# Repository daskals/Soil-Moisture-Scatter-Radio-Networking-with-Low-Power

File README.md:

# Soil-Moisture-Scatter-Radio-Networking-with-Low-Power
Hardware and Software files of  IEEE publication: Soil Moisture Scatter Radio Networking with Low Power

In this repo, a low-cost (6 Euro per sensor), low-power (in the order of 200 µW per sensor), with high communication range (in the order of 250 meter), scatter radio sensor network is presented, for soil moisture monitoring at multiple locations. The proposed network utilizes analog frequency modulation (FM) in a bistatic network
architecture (i.e., the emitter and reader are not co-located), while
the sensors operate simultaneously, using frequency division
multiple access (FDMA). In contrast to prior art, this work
utilizes an ultra-low cost software-defined radio reader, offers
custom microstrip capacitive sensing with simple calibration, as
well as modulation pulses for each scatter radio sensor with
50% duty cycle; the latter is necessary for scalable network
designs. Overall root mean squared error (RMSE) below 1% is observed, even for ranges of 250 m. This is another small (but concrete) step for the adoption of scatter radio technology as a
key enabling technology for scalable, large-scale, low-power and cost environmental sensor networking.
---

IEEE Xplore: https://ieeexplore.ieee.org/document/7490345/ \
Local: http://www.daskalakispiros.com/files/daskalakis_mtt_2015.pdf

---
**Questions/issues**
Inquiries regarding the scripts provided are cordially welcome.

---
**Citing**

If you use our algorithm, please cite [[1]](https://ieeexplore.ieee.org/document/7490345/).

```bibtex
@article{daskalakis2016soil,
  title={Soil moisture scatter radio networking with low power},
  author={Daskalakis, Spyridon-Nektarios and Assimonis, Stylianos D and Kampianakis, Eleftherios and Bletsas, Aggelos},
  journal={IEEE Transactions on Microwave Theory and Techniques},
  volume={64},
  number={7},
  pages={2338--2346},
  year={2016},
  publisher={IEEE}
}
 
```

[[1]](https://ieeexplore.ieee.org/document/7490345/) S. N. Daskalakis, S.D. Assimonis, E. Kampianakis and A. Bletsas, Soil Moisture Scatter Radio Networking with Low Power, IEEE Transactions on Microwave Theory and Techniques (TMTT), Special Issue on RFID Sensing & Imaging, Vol. 64, No. 7, pp. 2338-2346, July 2016.

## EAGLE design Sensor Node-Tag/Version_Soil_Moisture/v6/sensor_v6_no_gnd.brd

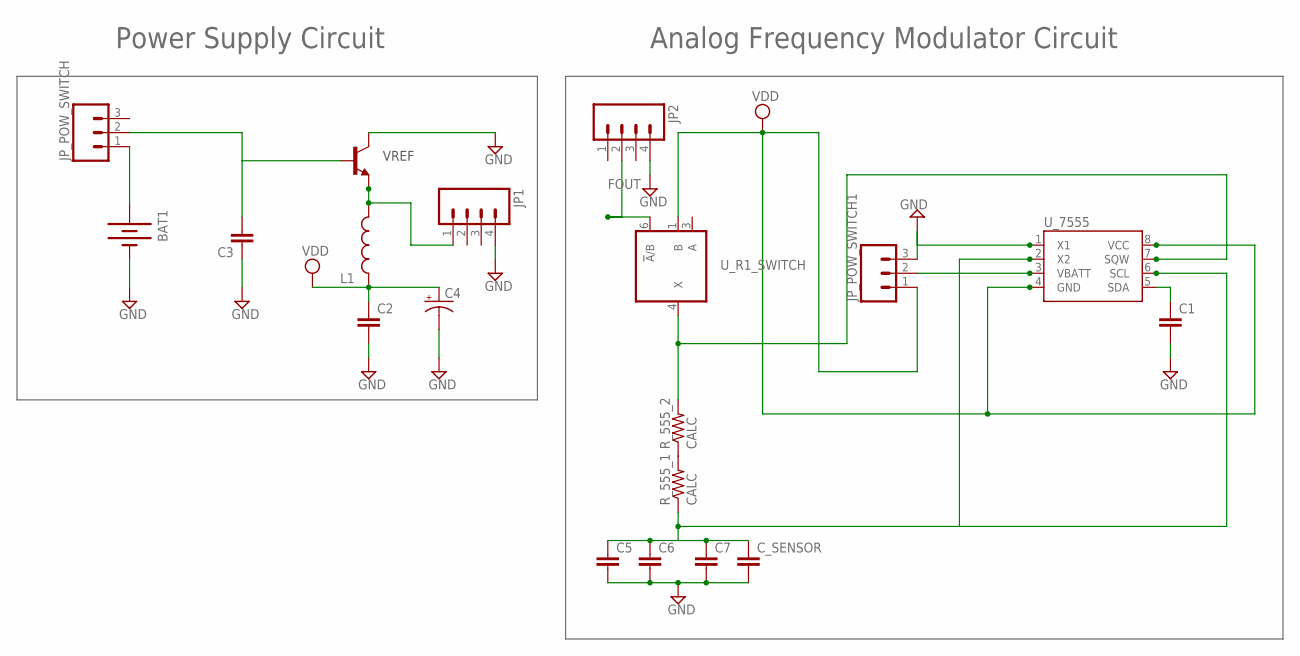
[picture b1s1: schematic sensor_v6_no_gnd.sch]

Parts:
BAT1: BATTERY20PTH_LAB; BATTCOM_20MM_PTH
C1, C2, C3: CAP0603-CAP; 0603-CAP
C4: CAP_POL1206; EIA3216
C5, C6, C7: CAP0805; 0805
C_SENSOR: CAP0805; 0805
JP1, JP2: M04LOCK; 1X04_LOCK
JP_POW_SWITCH, JP_POW_SWITCH1: M03LOCK; 1X03_LOCK
L1: INDUCTOR0603; 0603
R_555_1, R_555_2: CALC; 0805
U_7555: DS1307SO8; SO08
U_R1_SWITCH: 741G3157DCKR; DCK_R-PDSO-G6
U_VREF: TRANSISTOR_NPNSOT23-3; SOT23-3

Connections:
FOUT: JP2.2, JP_POW_SWITCH1.2, U_7555.3 (VBATT), U_R1_SWITCH.6 (!A!/B)
GND: BAT1.2 (-), C1.2, C2.2, C3.1, C4.C (-), C5.2, C6.2, C7.2, C_SENSOR.2, JP1.4, JP2.4, JP_POW_SWITCH1.3, U_7555.1 (X1), U_R1_SWITCH.2 (GND), U_VREF.3 (C)
unnamed: BAT1.1 (+), JP_POW_SWITCH.1
unnamed: R_555_1.2, R_555_2.1
P2: C5.1, C6.1, C7.1, C_SENSOR.1, R_555_1.1, U_7555.2 (X2), U_7555.6 (SCL)
P5: C1.1, U_7555.5 (SDA)
P7: R_555_2.2, U_7555.7 (SQW), U_R1_SWITCH.4 (X)
VCC: U_R1_SWITCH.5 (VCC)
VDD: C2.1, C4.A (+), JP_POW_SWITCH1.1, L1.1, U_7555.4 (GND), U_7555.8 (VCC), U_R1_SWITCH.1 (B)
VREFIN: C3.2, JP_POW_SWITCH.2, U_VREF.1 (B)
VREFOUT: JP1.1, L1.2, U_VREF.2 (E)

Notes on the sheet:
Power Supply Circuit
Analog Frequency Modulator Circuit
VREF

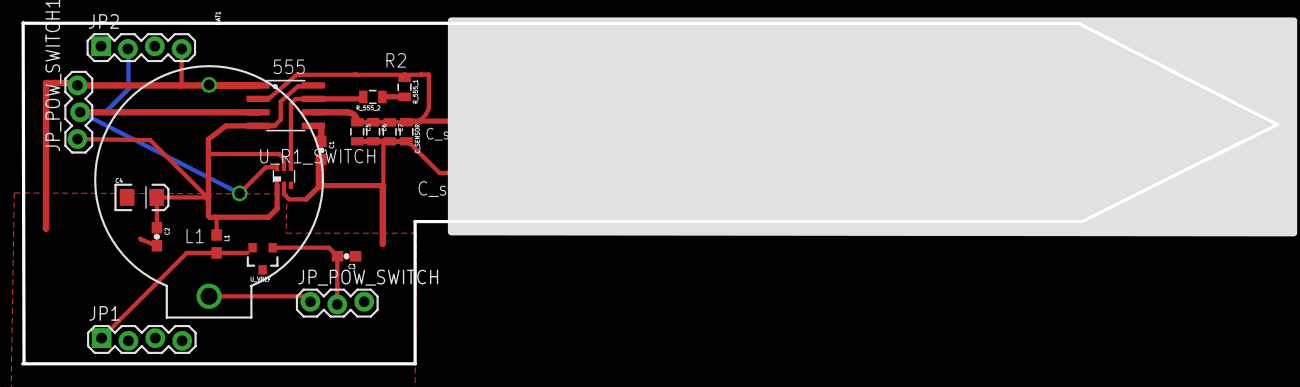
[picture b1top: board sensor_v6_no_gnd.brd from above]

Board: 2 copper layers, 118.6 x 32.2 mm, 19 parts (0 on the bottom side), 10 nets.

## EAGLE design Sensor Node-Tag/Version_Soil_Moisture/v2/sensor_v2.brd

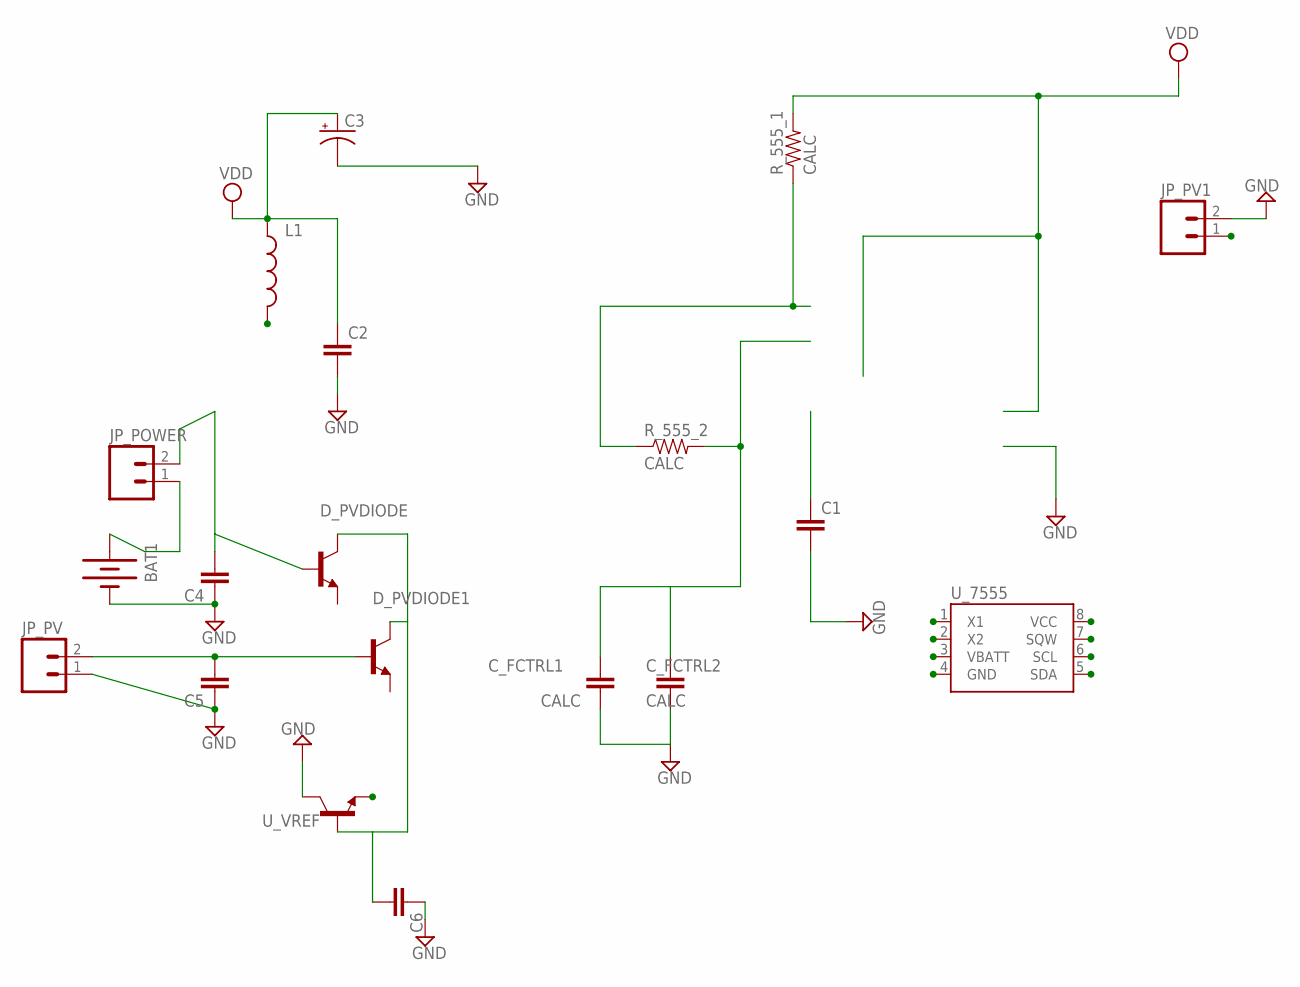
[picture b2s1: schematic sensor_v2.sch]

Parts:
BAT1: BATTERY20PTH_LAB; BATTCOM_20MM_PTH
C1, C2, C4, C5, C6: CAP0603-CAP; 0603-CAP
C3: CAP_POL1206; EIA3216
C_FCTRL1, C_FCTRL2: CALC; 0603-CAP
D_PVDIODE, D_PVDIODE1: TRANSISTOR_NPNSOT23-3; SOT23-3
JP_POWER: M02LOCK; 1X02_LOCK
JP_PV, JP_PV1: M02LOCK; 1X02_LOCK
L1: INDUCTOR0603; 0603
R_555_1: CALC; 0805
R_555_2: CALC; 0603-RES
U_7555: DS1307SO8; SO08
U_VREF: TRANSISTOR_NPNSOT23-3; SOT23-3

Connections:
FOUT: JP_PV1.1, U_7555.3 (VBATT)
GND: BAT1.2 (-), C1.2, C2.2, C3.C (-), C4.1, C5.1, C6.1, C_FCTRL1.2, C_FCTRL2.2, JP_PV.1, JP_PV1.2, U_7555.1 (X1), U_VREF.3 (C)
unnamed: C5.2, D_PVDIODE1.1 (B), JP_PV.2
unnamed: BAT1.1 (+), JP_POWER.1
unnamed: C4.2, D_PVDIODE.1 (B), JP_POWER.2
P2: C_FCTRL1.1, C_FCTRL2.1, R_555_2.2, U_7555.2 (X2), U_7555.6 (SCL)
P5: C1.1, U_7555.5 (SDA)
P7: R_555_1.1, R_555_2.1, U_7555.7 (SQW)
VDD: C2.1, C3.A (+), L1.1, R_555_1.2, U_7555.4 (GND), U_7555.8 (VCC)
VREFIN: C6.2, D_PVDIODE.3 (C), D_PVDIODE1.3 (C), U_VREF.1 (B)
VREFOUT: L1.2, U_VREF.2 (E)

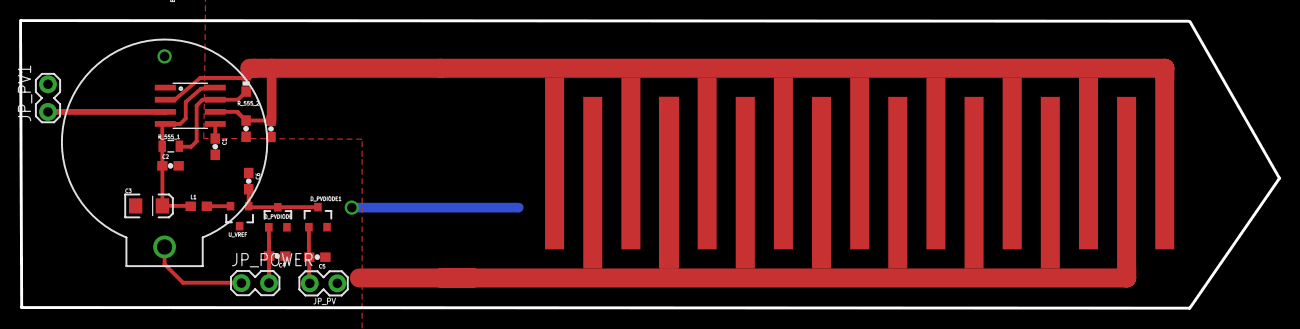
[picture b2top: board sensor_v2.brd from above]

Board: 2 copper layers, 132.1 x 30.2 mm, 19 parts (0 on the bottom side), 11 nets.

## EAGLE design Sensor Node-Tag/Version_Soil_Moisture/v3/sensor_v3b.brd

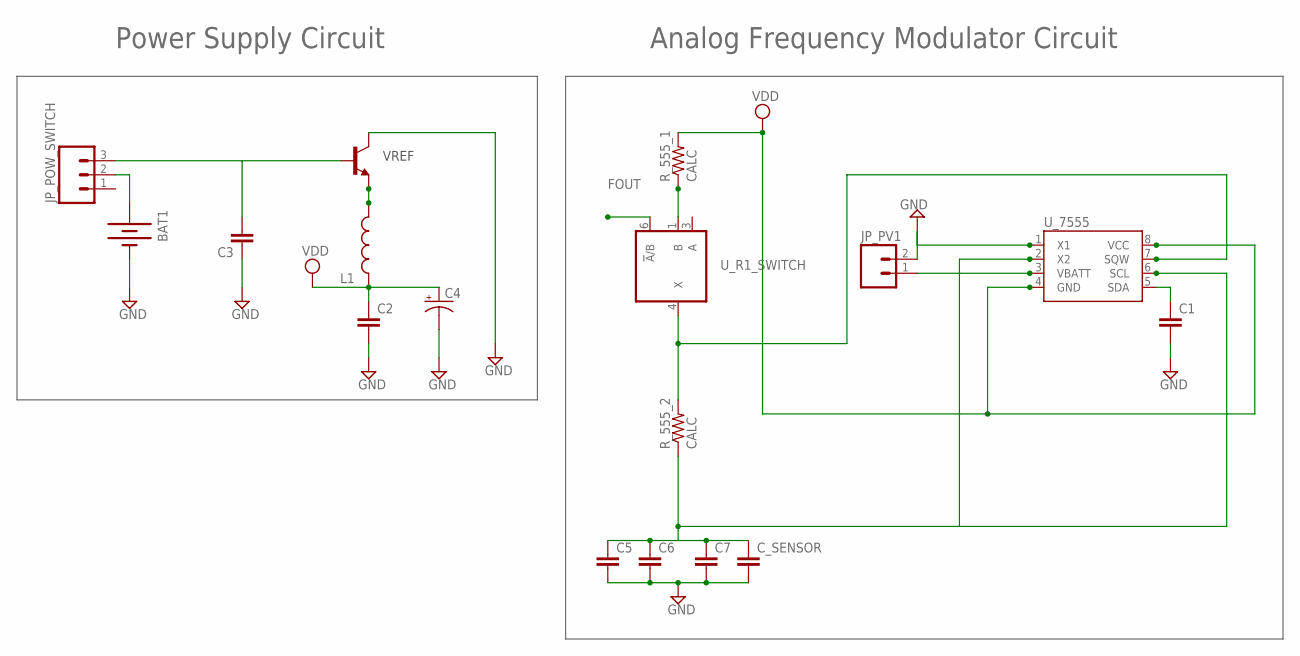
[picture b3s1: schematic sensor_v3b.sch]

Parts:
BAT1: BATTERY20PTH_LAB; BATTCOM_20MM_PTH
C1, C2, C3: CAP0603-CAP; 0603-CAP
C4: CAP_POL1206; EIA3216
C5, C6, C7: CAP0805; 0805
C_SENSOR: CAP0805; 0805
JP_POW_SWITCH: M03LOCK; 1X03_LOCK
JP_PV1: M02LOCK; 1X02_LOCK
L1: INDUCTOR0603; 0603
R_555_1, R_555_2: CALC; 0805
U_7555: DS1307SO8; SO08
U_R1_SWITCH: 741G3157DCKR; DCK_R-PDSO-G6
U_VREF: TRANSISTOR_NPNSOT23-3; SOT23-3

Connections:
FOUT: JP_PV1.1, U_7555.3 (VBATT), U_R1_SWITCH.6 (!A!/B)
GND: BAT1.2 (-), C1.2, C2.2, C3.1, C4.C (-), C5.2, C6.2, C7.2, C_SENSOR.2, JP_PV1.2, U_7555.1 (X1), U_R1_SWITCH.2 (GND), U_VREF.3 (C)
unnamed: BAT1.1 (+), JP_POW_SWITCH.2
P2: C5.1, C6.1, C7.1, C_SENSOR.1, R_555_2.1, U_7555.2 (X2), U_7555.6 (SCL)
P5: C1.1, U_7555.5 (SDA)
P7: R_555_2.2, U_7555.7 (SQW), U_R1_SWITCH.4 (X)
R1: R_555_1.1, U_R1_SWITCH.1 (B)
VCC: U_R1_SWITCH.5 (VCC)
VDD: C2.1, C4.A (+), L1.1, R_555_1.2, U_7555.4 (GND), U_7555.8 (VCC)
VREFIN: C3.2, JP_POW_SWITCH.3, U_VREF.1 (B)
VREFOUT: L1.2, U_VREF.2 (E)

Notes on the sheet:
Power Supply Circuit
Analog Frequency Modulator Circuit
VREF

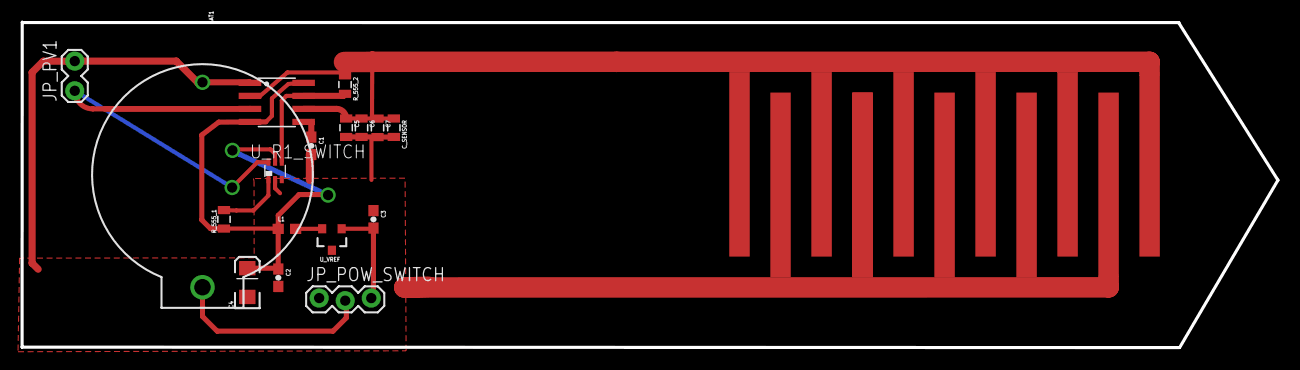
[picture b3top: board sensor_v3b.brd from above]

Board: 2 copper layers, 122.5 x 31.8 mm, 17 parts (0 on the bottom side), 10 nets.

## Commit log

2017-01-12 Create me
2017-01-12 Update and rename me to DownloadSoft
2017-01-12 Set theme jekyll-theme-time-machine

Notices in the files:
parts and their libraries:
SparkFun-Resistors: Licensing: CC v3.0 Share-Alike You are welcome to use this library for commercial purposes.
